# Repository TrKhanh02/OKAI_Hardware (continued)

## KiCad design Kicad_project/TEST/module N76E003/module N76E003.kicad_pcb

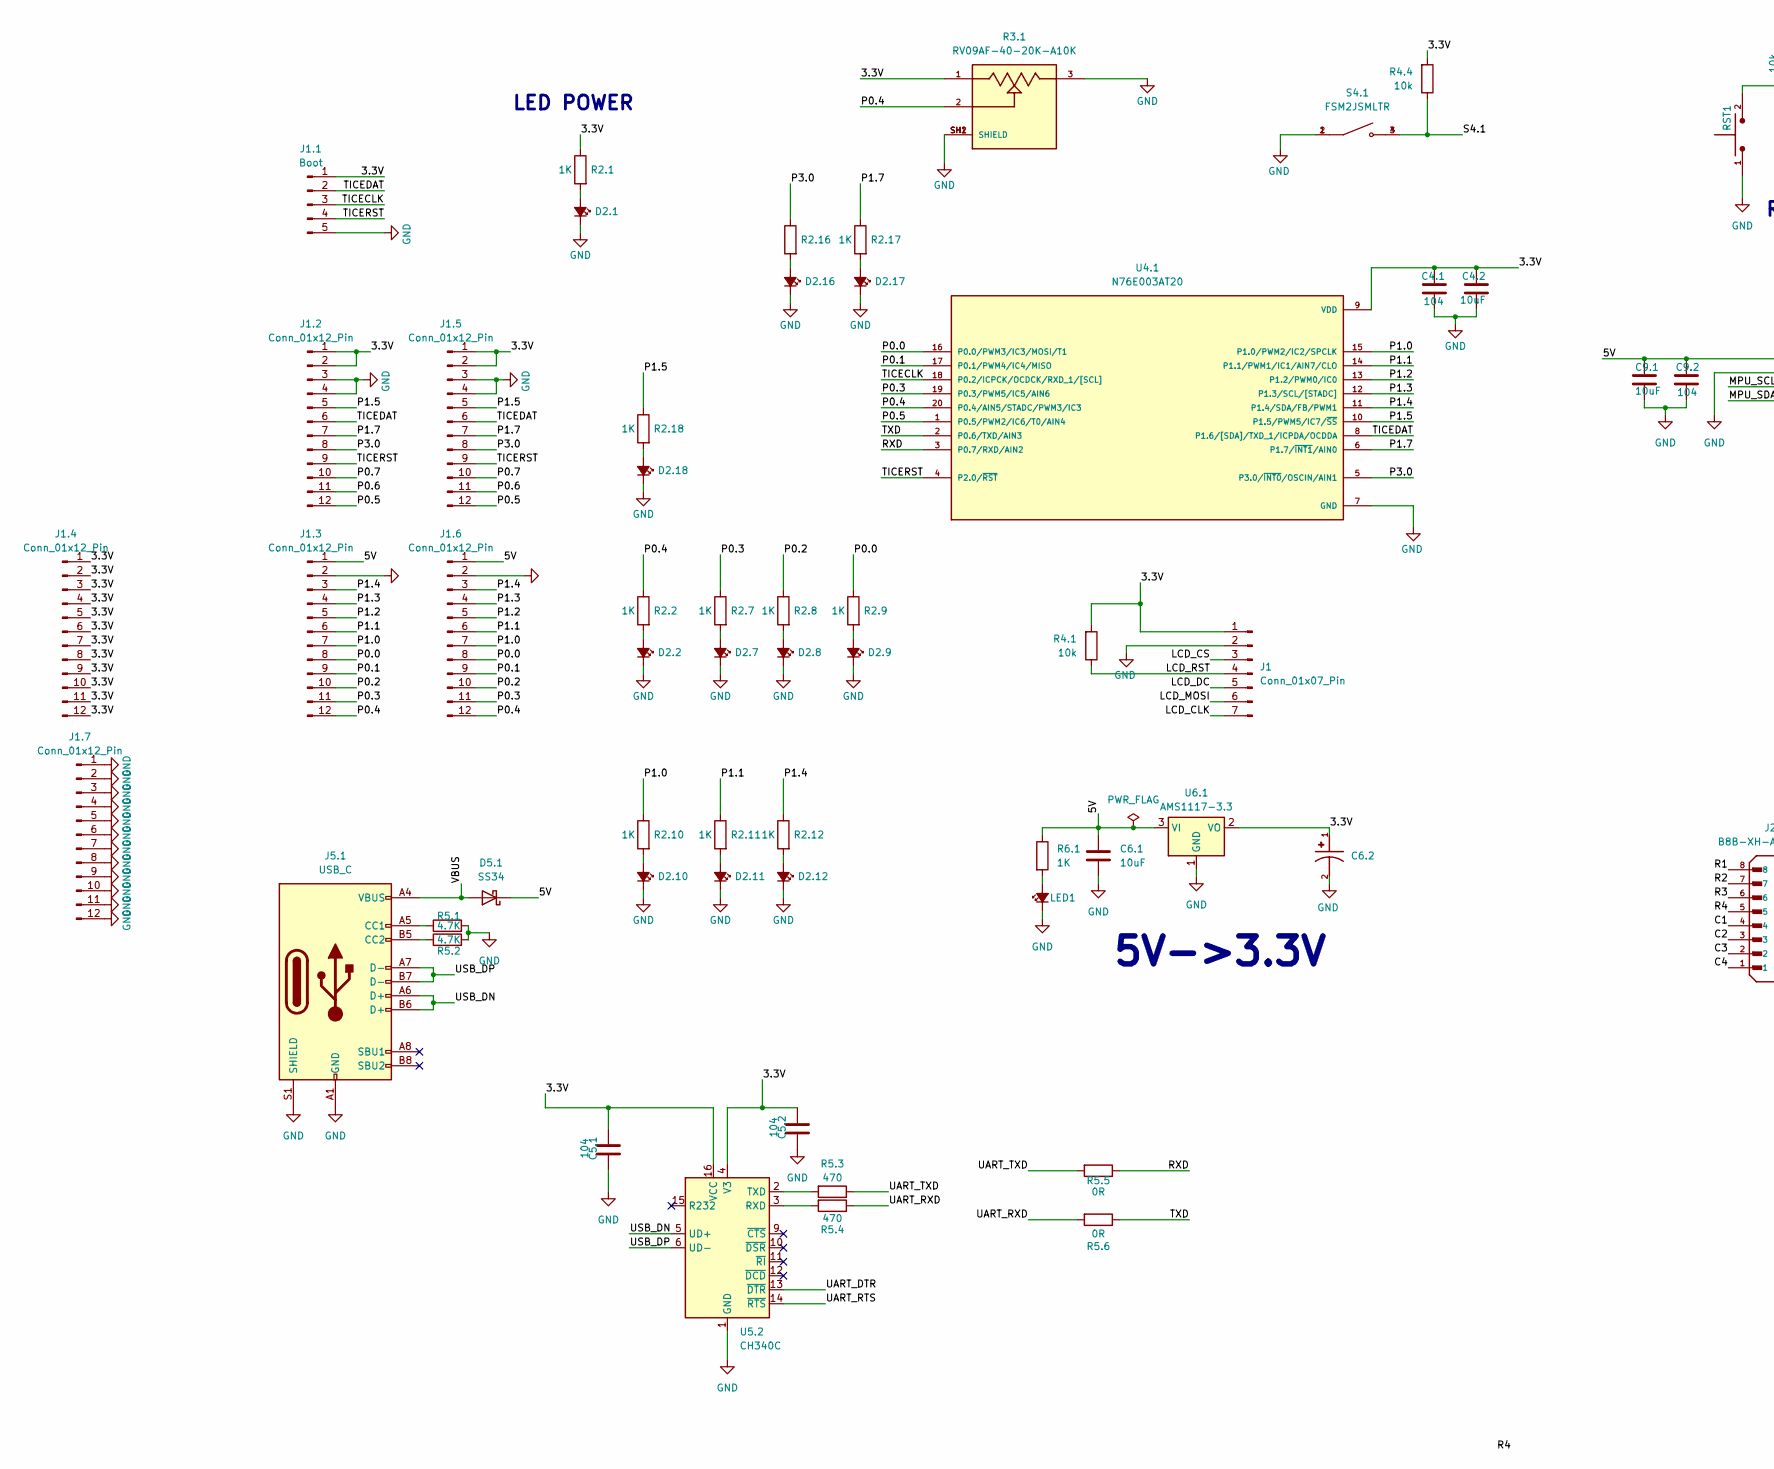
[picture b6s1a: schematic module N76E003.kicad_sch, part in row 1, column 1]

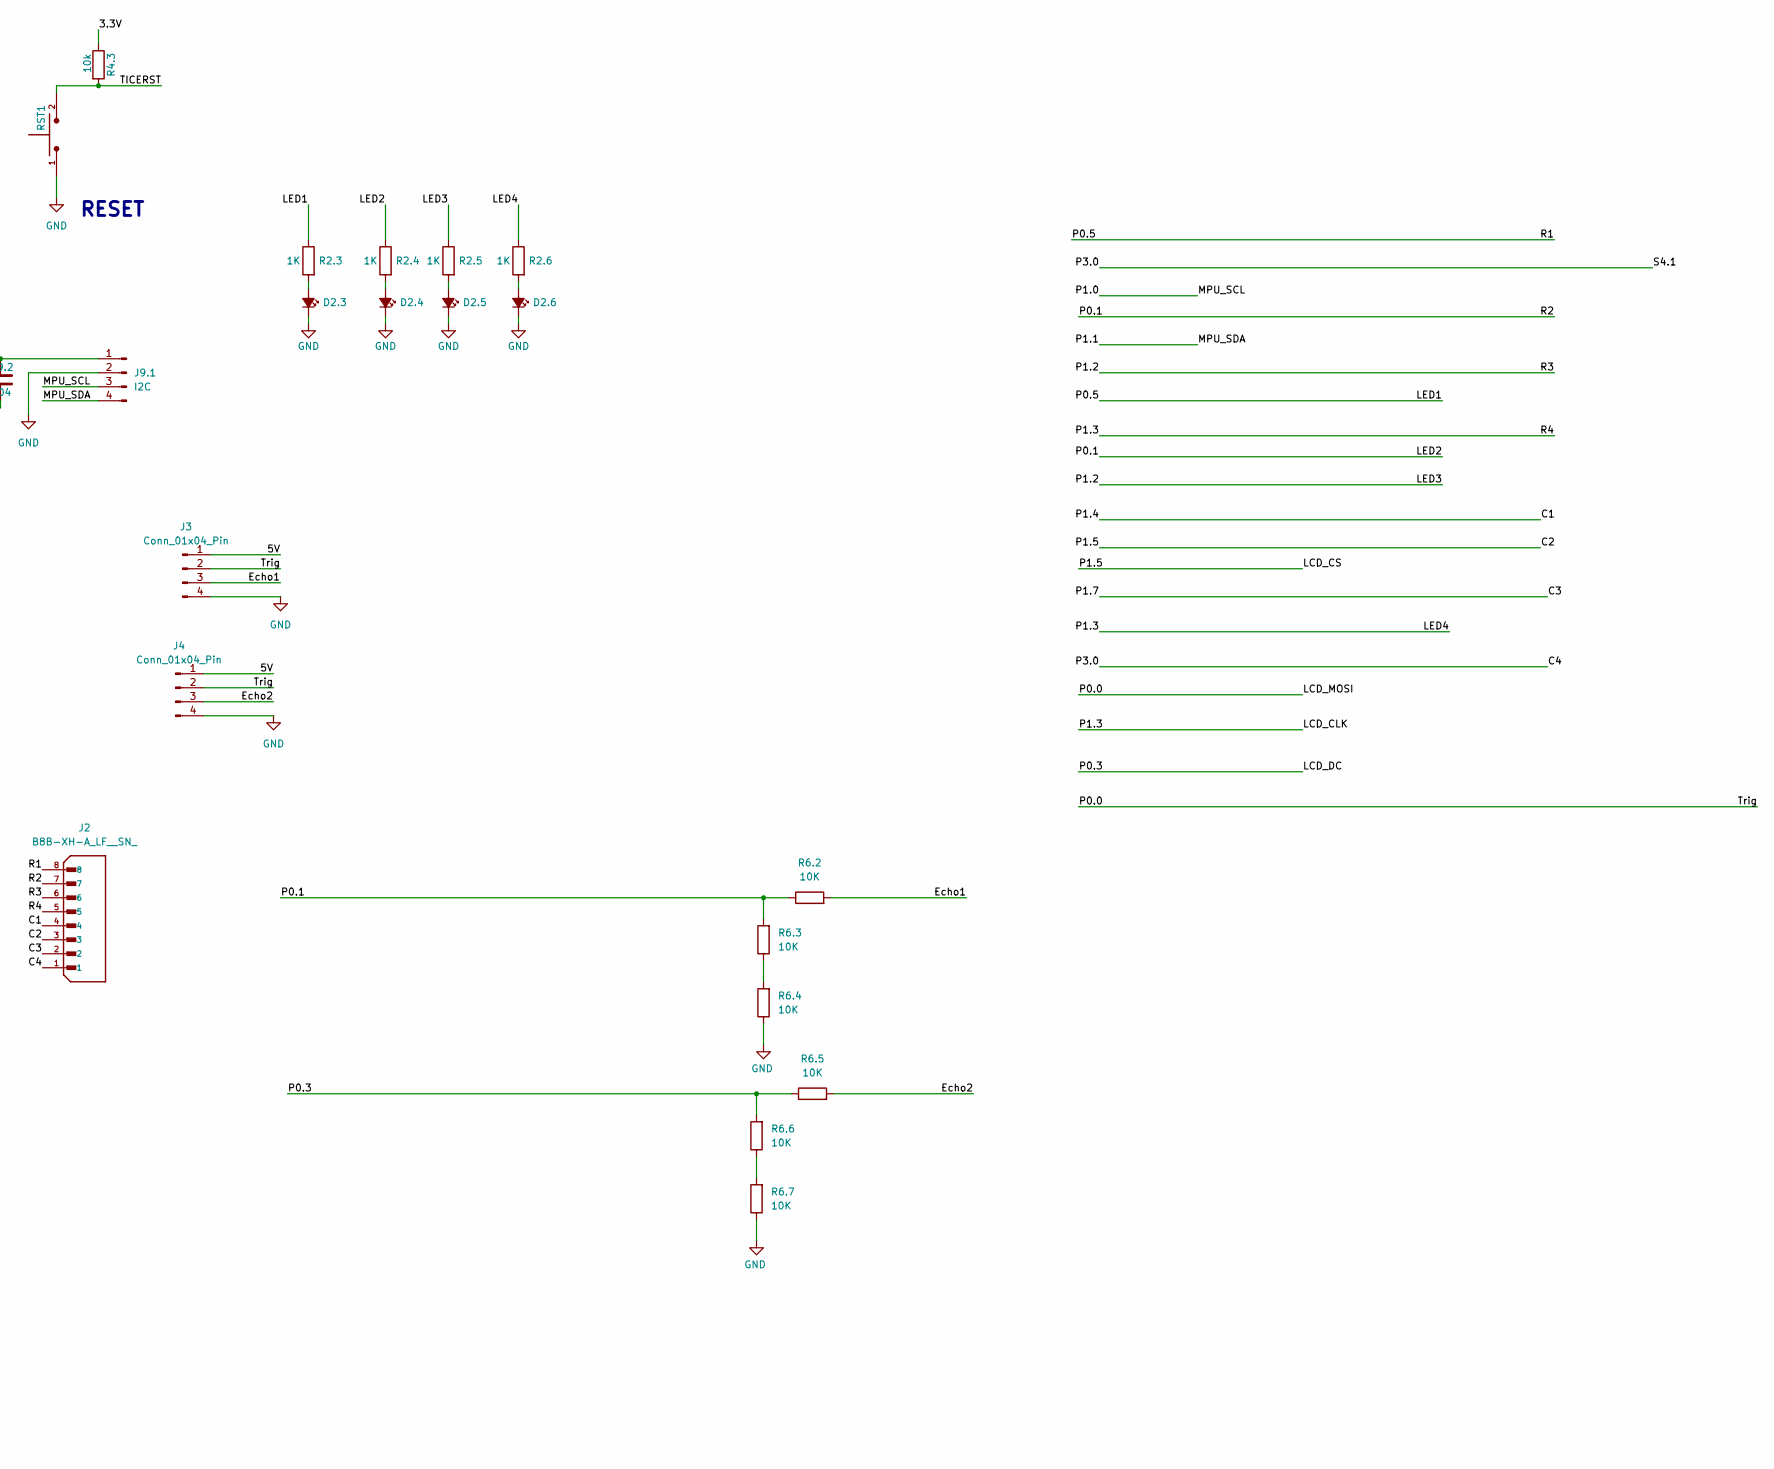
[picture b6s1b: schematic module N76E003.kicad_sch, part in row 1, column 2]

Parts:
C4.1, C5.1, C5.2, C9.2: 104; C_0805_2012Metric_Pad1.18x1.45mm_HandSolder
C4.2, C6.1, C9.1: 10uF; C_0805_2012Metric_Pad1.18x1.45mm_HandSolder
C6.2: 100uF; CAPMP3216X180N; PARTREV 031320
D2.1, D2.2, D2.3, D2.4, D2.5, D2.6, D2.7, D2.8, D2.9, D2.10, D2.11, D2.12, D2.16, D2.17, D2.18: LED_Small_Filled; LED_0805_2012Metric_Pad1.15x1.40mm_HandSolder
D5.1: SS34; D_SMA
J1: Conn_01x07_Pin; PinSocket_1x07_P2.54mm_Vertical
J1.1: Boot; PinHeader_1x05_P2.54mm_Vertical
J1.2, J1.3, J1.4, J1.5, J1.6, J1.7: Conn_01x12_Pin; PinHeader_1x12_P2.54mm_Vertical
J2: B8B-XH-A_LF__SN_; JST_B8B-XH-A_LF__SN_; PARTREV 7/4/21
J3, J4: Conn_01x04_Pin; PinHeader_1x04_P2.54mm_Vertical
J5.1: USB_C; USB_C_Receptacle_HRO_TYPE-C-31-M-12
J9.1: I2C; PinSocket_1x04_P2.54mm_Vertical
LED1: LED_Small_Filled; LED_0805_2012Metric_Pad1.15x1.40mm_HandSolder
R2.1, R2.2, R2.3, R2.4, R2.5, R2.6, R2.7, R2.8, R2.9, R2.10, R2.11, R2.12, R2.16, R2.17, R2.18, R6.1: 1K; R_0805_2012Metric_Pad1.20x1.40mm_HandSolder
R3.1: RV09AF-40-20K-A10K; TRIM_RV09AF-40-20K-A10K; PARTREV N/A
R4.1, R4.3, R4.4: 10k; R_0805_2012Metric_Pad1.20x1.40mm_HandSolder
R5.1, R5.2: 4.7K; R_0805_2012Metric_Pad1.20x1.40mm_HandSolder
R5.3, R5.4: 470; R_0805_2012Metric_Pad1.20x1.40mm_HandSolder
R5.5, R5.6: 0R; R_0805_2012Metric_Pad1.20x1.40mm_HandSolder
R6.2, R6.3, R6.4, R6.5, R6.6, R6.7: 10K; R_0805_2012Metric_Pad1.20x1.40mm_HandSolder
RST1: TS10-63-26-BE-250-SMT-TR; SW_TS10-63-26-BE-250-SMT-TR; PARTREV 1.0
S4.1: FSM2JSMLTR; SW_1571527-2; PARTREV V
U4.1: N76E003AT20; SOP65P640X120-20N; PARTREV 1.04
U5.2: CH340C; SOIC-16_3.9x9.9mm_P1.27mm
U6.1: AMS1117-3.3; SOT-223-3_TabPin2

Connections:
/3.3V: C4.1.1, C4.2.1, C5.1.2, C5.2.2, C6.2.1, J1.1, J1.1.1, J1.2.1, J1.2.2, J1.4.1, J1.4.2, J1.4.3, J1.4.4, J1.4.5, J1.4.6, J1.4.7, J1.4.8, J1.4.9, J1.4.10, J1.4.11, J1.4.12, J1.5.1, J1.5.2, R2.1.1, R3.1.1, R4.1.2, R4.3.1, R4.4.2, U4.1.9 (VDD), U5.2.4 (V3), U5.2.16 (VCC), U6.1.2 (VO)
/5V: C6.1.1, C9.1.1, C9.2.1, D5.1.1 (K), J1.3.1, J1.6.1, J3.1, J4.1, J9.1.1, R6.1.1, U6.1.3 (VI)
/C1: J1.3.3, J1.6.3, J2.4, R2.12.1, U4.1.11 (P1.4/SDA/FB/PWM1)
/C2: J1.3, J1.2.5, J1.5.5, J2.3, R2.18.1, U4.1.10 (P1.5/PWM5/IC7/~SS)
/C3: J1.2.7, J1.5.7, J2.2, R2.17.1, U4.1.6 (P1.7/~INT1/AIN0)
/C4: J1.2.8, J1.5.8, J2.1, R2.16.1, R4.4.1, S4.1.3, S4.1.4, U4.1.5 (P3.0/~INT0/OSCIN/AIN1)
/Echo1: J3.3, R6.2.2
/Echo2: J4.3, R6.5.2
/LCD_CLK: J1.7, J1.3.4, J1.6.4, J2.5, R2.6.1, U4.1.12 (P1.3/SCL/[STADC])
/LCD_DC: J1.5, J1.3.11, J1.6.11, R2.7.1, R6.5.1, R6.6.2, U4.1.19 (P0.3/PWM5/IC5/AIN6)
/LCD_MOSI: J1.6, J1.3.8, J1.6.8, J3.2, J4.2, R2.9.1, U4.1.16 (P0.0/PWM3/IC3/MOSI/T1)
/LCD_RST: J1.4, R4.1.1
/LED1: J1.2.12, J1.5.12, J2.8, R2.3.1, U4.1.1 (P0.5/PWM2/IC6/T0/AIN4)
/LED2: J1.3.9, J1.6.9, J2.7, R2.4.1, R6.2.1, R6.3.2, U4.1.17 (P0.1/PWM4/IC4/MISO)
/LED3: J1.3.5, J1.6.5, J2.6, R2.5.1, U4.1.13 (P1.2/PWM0/IC0)
/MPU_SCL: J1.3.7, J1.6.7, J9.1.3, R2.10.1, U4.1.15 (P1.0/PWM2/IC2/SPCLK)
/MPU_SDA: J1.3.6, J1.6.6, J9.1.4, R2.11.1, U4.1.14 (P1.1/PWM1/IC1/AIN7/CLO)
/P0.2: J1.3.10, J1.6.10, R2.8.1
/P0.4: J1.3.12, J1.6.12, R2.2.1, R3.1.2, U4.1.20 (P0.4/AIN5/STADC/PWM3/IC3)
/P0.6: J1.2.11, J1.5.11
/P0.7: J1.2.10, J1.5.10
/RXD: R5.5.1, U4.1.3 (P0.7/RXD/AIN2)
/TICECLK: J1.1.3, U4.1.18 (P0.2/ICPCK/OCDCK/RXD_1/[SCL])
/TICEDAT: J1.1.2, J1.2.6, J1.5.6, U4.1.8 (P1.6/[SDA]/TXD_1/ICPDA/OCDDA)
/TICERST: J1.1.4, J1.2.9, J1.5.9, R4.3.2, RST1.2, U4.1.4 (P2.0/~RST)
/TXD: R5.6.1, U4.1.2 (P0.6/TXD/AIN3)
/UART_DTR: U5.2.13 (~DTR)
/UART_RTS: U5.2.14 (~RTS)
/UART_RXD: R5.4.1, R5.6.2
/UART_TXD: R5.3.1, R5.5.2
/USB_DN: J5.1.A6 (D+), J5.1.B6 (D+), U5.2.5 (UD+)
/USB_DP: J5.1.A7 (D-), J5.1.B7 (D-), U5.2.6 (UD-)
/VBUS: D5.1.2 (A), J5.1.A4 (VBUS), J5.1.A9 (VBUS), J5.1.B4 (VBUS), J5.1.B9 (VBUS)
GND: C4.1.2, C4.2.2, C5.1.1, C5.2.1, C6.1.2, C6.2.2, C9.1.2, C9.2.2, D2.1.1 (K), D2.2.1 (K), D2.3.1 (K), D2.4.1 (K), D2.5.1 (K), D2.6.1 (K), D2.7.1 (K), D2.8.1 (K), D2.9.1 (K), D2.10.1 (K), D2.11.1 (K), D2.12.1 (K), D2.16.1 (K), D2.17.1 (K), D2.18.1 (K), J1.2, J1.1.5, J1.2.3, J1.2.4, J1.3.2, J1.5.3, J1.5.4, J1.6.2, J1.7.1, J1.7.2, J1.7.3, J1.7.4, J1.7.5, J1.7.6, J1.7.7, J1.7.8, J1.7.9, J1.7.10, J1.7.11, J1.7.12, J3.4, J4.4, J5.1.A1 (GND), J5.1.A12 (GND), J5.1.B1 (GND), J5.1.B12 (GND), J5.1.S1 (SHIELD), J9.1.2, LED1.1 (K), R3.1.3, R3.1.SH1 (SHIELD), R3.1.SH2 (SHIELD), R5.1.2, R5.2.2, R6.4.1, R6.7.1, RST1.1, S4.1.1, S4.1.2, U4.1.7 (GND), U5.2.1 (GND), U6.1.1 (GND)
unnamed: D2.1.2 (A), R2.1.2
unnamed: D2.2.2 (A), R2.2.2
unnamed: D2.3.2 (A), R2.3.2
unnamed: D2.4.2 (A), R2.4.2
unnamed: D2.5.2 (A), R2.5.2
unnamed: D2.6.2 (A), R2.6.2
unnamed: D2.7.2 (A), R2.7.2
unnamed: D2.8.2 (A), R2.8.2
unnamed: D2.9.2 (A), R2.9.2
unnamed: D2.10.2 (A), R2.10.2
unnamed: D2.11.2 (A), R2.11.2
unnamed: D2.12.2 (A), R2.12.2
unnamed: D2.16.2 (A), R2.16.2
unnamed: D2.17.2 (A), R2.17.2
unnamed: D2.18.2 (A), R2.18.2
unnamed: J5.1.A5 (CC1), R5.1.1
unnamed: J5.1.B5 (CC2), R5.2.1
unnamed: LED1.2 (A), R6.1.2
unnamed: R6.3.1, R6.4.2
unnamed: R6.6.1, R6.7.2
unnamed: R5.4.2, U5.2.3 (RXD)
unnamed: R5.3.2, U5.2.2 (TXD)

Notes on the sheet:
RESET
5V->3.3V
LED POWER

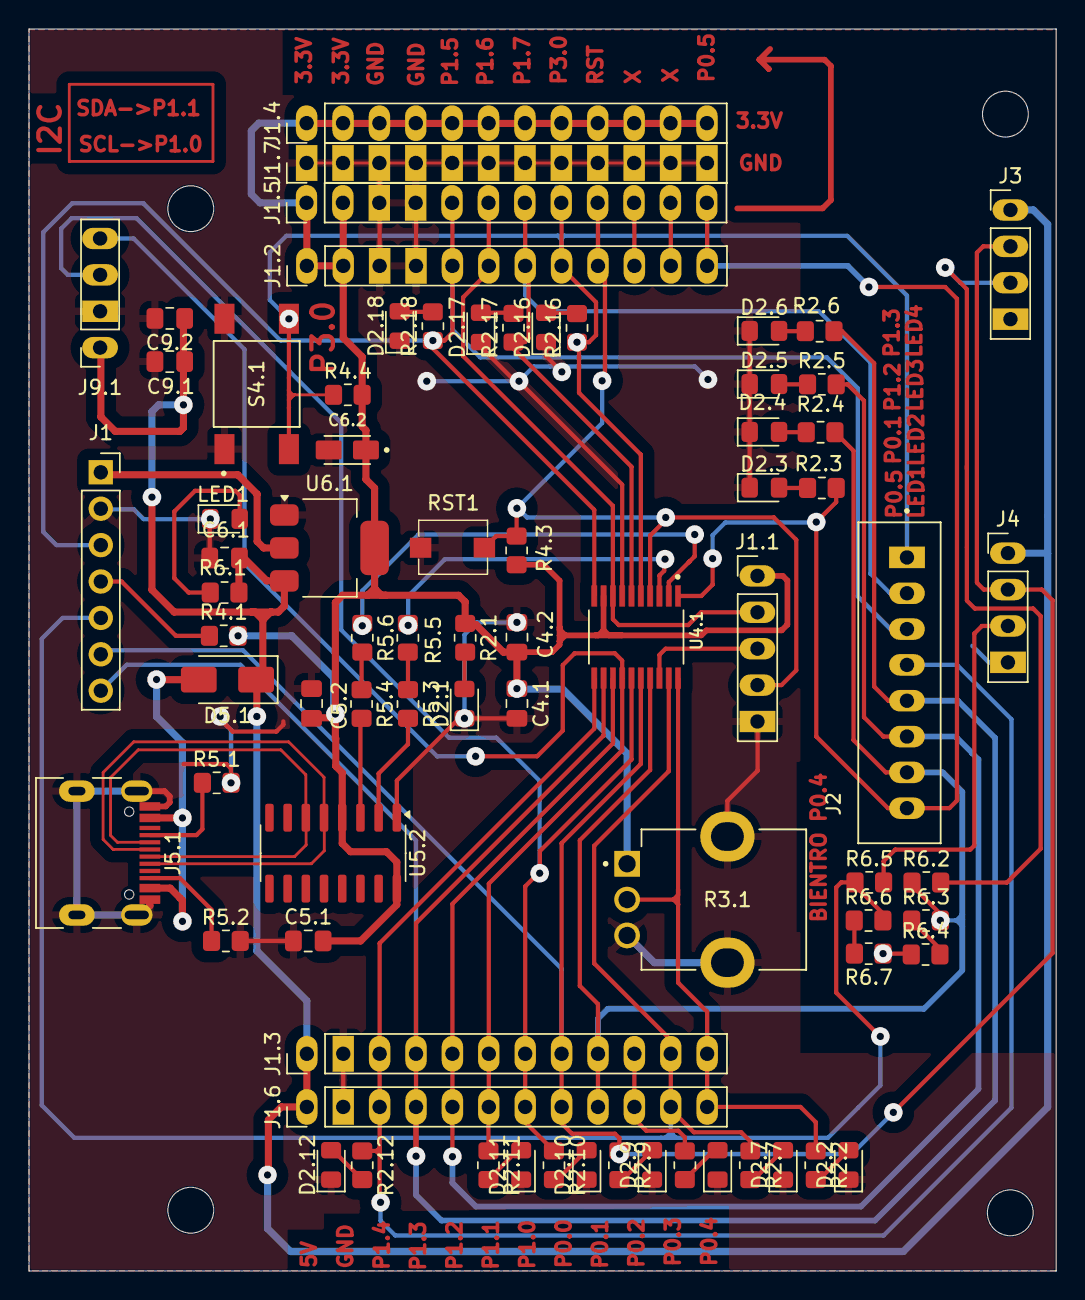
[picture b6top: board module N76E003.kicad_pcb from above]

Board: 2 copper layers, 71.7 x 86.7 mm, 75 parts (0 on the bottom side), 54 nets.
